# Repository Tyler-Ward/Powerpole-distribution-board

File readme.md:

# DC Distribution board for Anderson power-pole connectors.

This project is a fused DC distribution board.
The design uses Anderson powerpoles and ATC/ATO fuses which are in common use in amateur radio.
Unlike other DIY solutions this uses the powerpole 45A PCB contacts rather than short stubs of solid wire crimped to the powerpoles.

## Required parts

* 1*PCB - Should be made on a 2oz copper board.
* 4*Acrylic layers - one of each layer 3 at 6mm thick and one at 3mm thick
* 6*Anderson power pole connector pairs with 45A PCB connectors.
* 6*ATO fuse holders
* 6*330ohm resistors
* 6*3mm LEDs - bidirectional LEDs allow for fuse failure indication for both source and sinks
* 6*0.1uF Bypass capacitors

## Production files and Assembly instructions

Production files for the PCB and acrylic can be found in the releases list on github.
Assembly instructions can be found at https://www.suws.org.uk/wiki/Powerpole_Distribution

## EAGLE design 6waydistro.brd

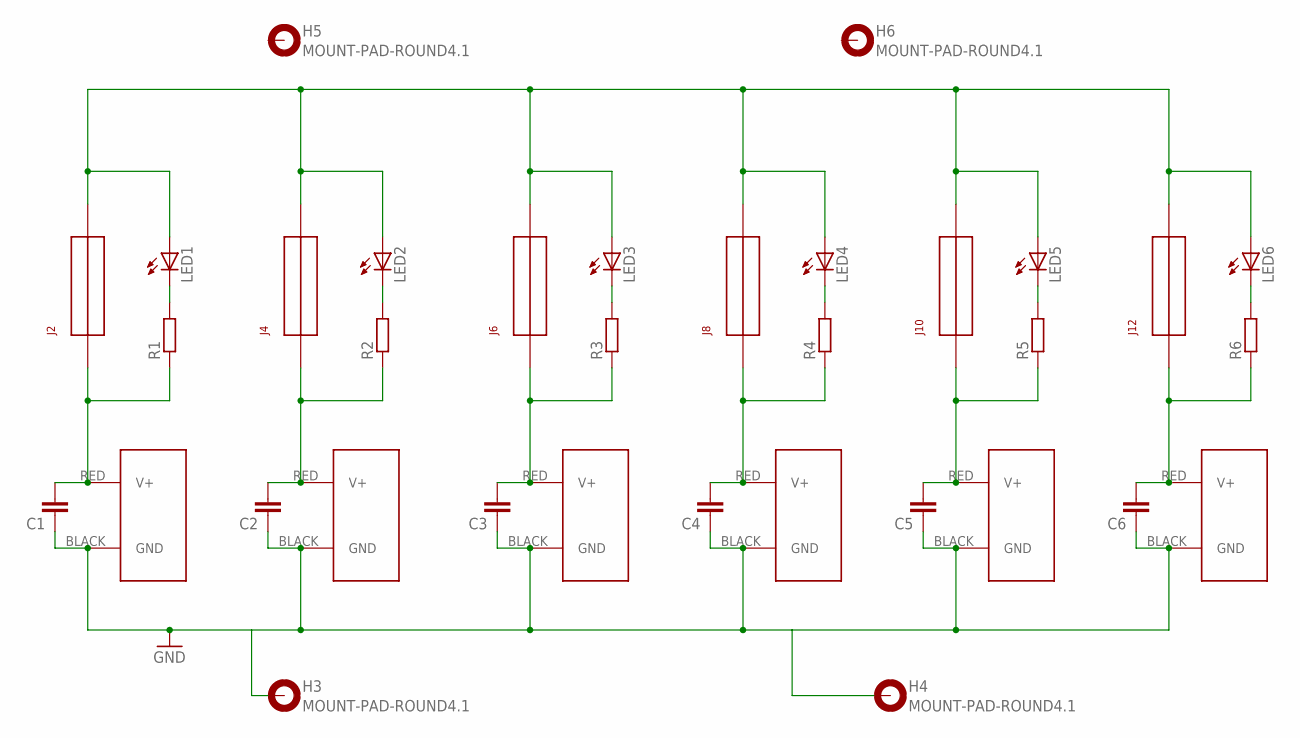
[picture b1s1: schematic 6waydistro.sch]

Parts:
C1, C2, C3, C4, C5, C6: C-EU050-025X075; C050-025X075
H3, H4, H5, H6: MOUNT-PAD-ROUND4.1; 4,1-PAD
J1, J3, J5, J7, J9, J11: POWERPOLE_POWER45A; POWERPOLE_PAIR_45A
J2, J4, J6, J8, J10, J12: FUSEATC; FUSE_ATC
LED1, LED2, LED3, LED4, LED5, LED6: LED3MM
R1, R2, R3, R4, R5, R6: R-EU_0204/7; 0204/7

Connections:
GND: C1.1, C2.1, C3.1, C4.1, C5.1, C6.1, H3.B4,1, H4.B4,1, J1.BLACK (GND), J3.BLACK (GND), J5.BLACK (GND), J7.BLACK (GND), J9.BLACK (GND), J11.BLACK (GND)
unnamed: LED2.K (C), R2.2
unnamed: LED1.K (C), R1.2
unnamed: LED3.K (C), R3.2
unnamed: LED4.K (C), R4.2
unnamed: LED5.K (C), R5.2
unnamed: LED6.K (C), R6.2
PPV1: C1.2, J1.RED (V+), J2.P$1, J2.P$2, R1.1
PPV2: C2.2, J3.RED (V+), J4.P$1, J4.P$2, R2.1
PPV3: C3.2, J5.RED (V+), J6.P$1, J6.P$2, R3.1
PPV4: C4.2, J7.RED (V+), J8.P$1, J8.P$2, R4.1
PPV5: C5.2, J9.RED (V+), J10.P$1, J10.P$2, R5.1
PPV6: C6.2, J11.RED (V+), J12.P$1, J12.P$2, R6.1
VCC: J2.P$3, J2.P$4, J4.P$3, J4.P$4, J6.P$3, J6.P$4, J8.P$3, J8.P$4, J10.P$3, J10.P$4, J12.P$3, J12.P$4, LED1.A, LED2.A, LED3.A, LED4.A, LED5.A, LED6.A

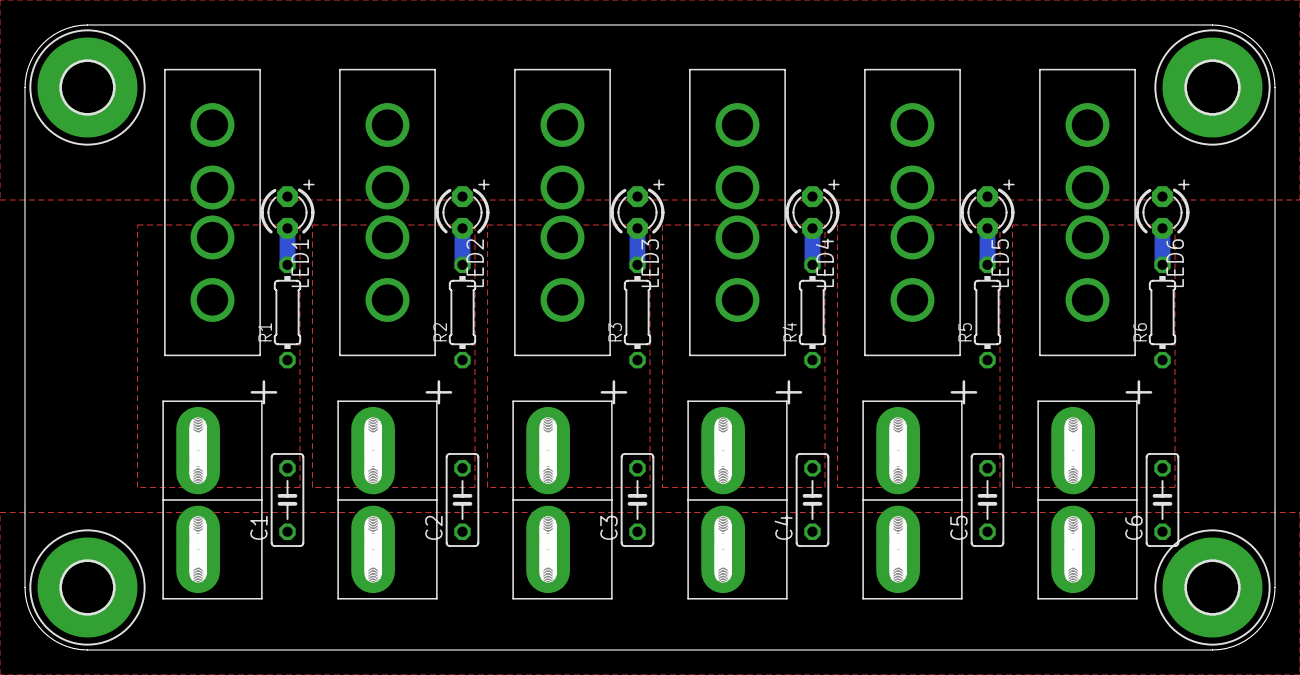
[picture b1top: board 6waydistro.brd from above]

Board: 2 copper layers, 100.0 x 50.0 mm, 34 parts (0 on the bottom side), 14 nets.

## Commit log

2014-04-19 added draft version of powerpole distro board
2016-03-25 Removed wire inlet holes and adjusted board layout for acrylic case
2016-03-26 Added gitignore and readme
2018-06-05 Minor silk screen edits to clean up component name placement
2018-06-05 Moved PCB files to separate directory
2018-06-05 Added Inventor cad files
